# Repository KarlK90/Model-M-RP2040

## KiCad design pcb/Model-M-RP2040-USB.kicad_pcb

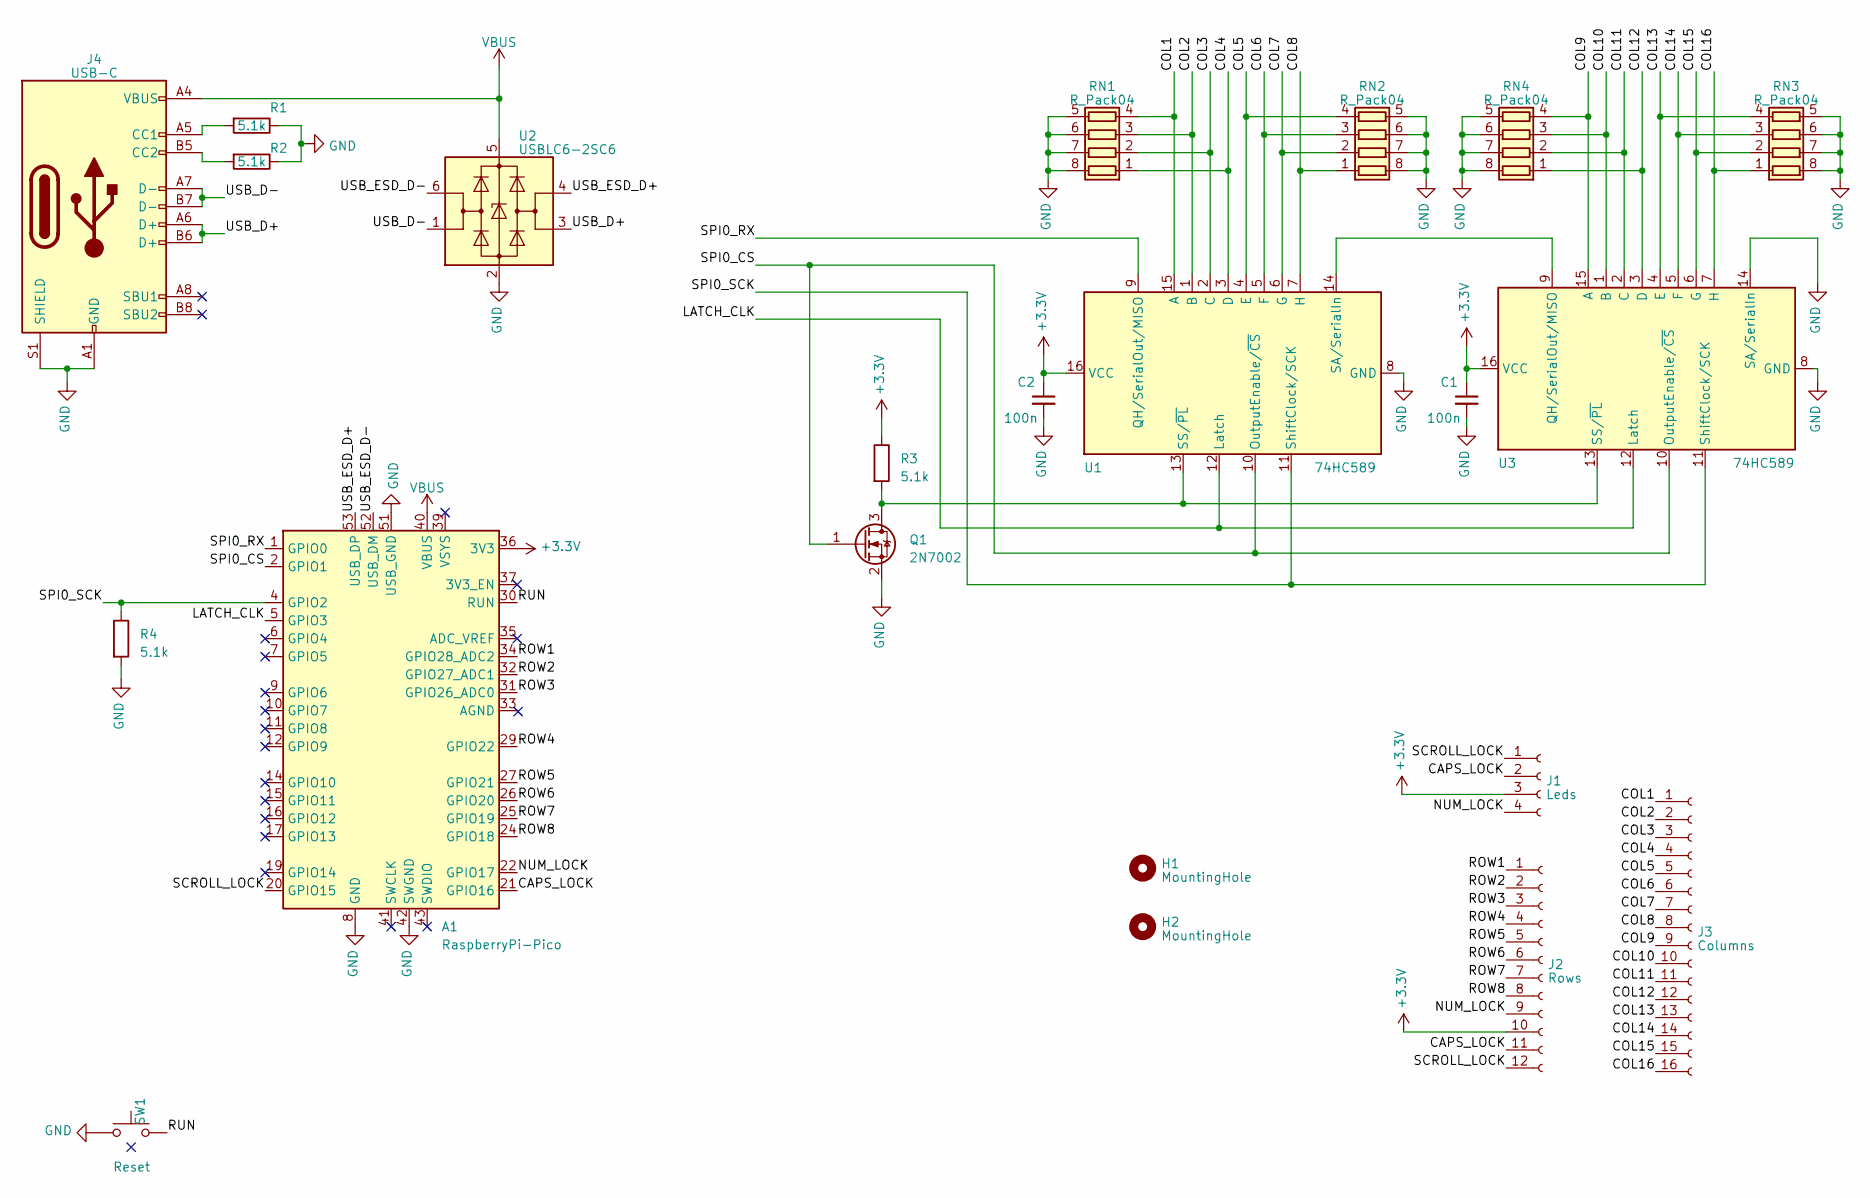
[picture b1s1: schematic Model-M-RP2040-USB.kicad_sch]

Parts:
A1: RaspberryPi-Pico; Raspberry_Pi_Pico_SMT_THT
C1, C2: 100n; C_0603_1608Metric
H1, H2: MountingHole; MountingHole_3.5mm
J1: Leds; PinSocket_1x04_P2.54mm_Vertical
J2: Rows; PinSocket_1x12_P2.54mm_Vertical
J3: Columns; PinSocket_1x16_P2.54mm_Vertical
J4: USB-C; HRO-TYPE-C-31-M-12-HandSoldering-NoSBU
Q1: 2N7002; SOT-23
R1, R2, R3, R4: 5.1k; R_0603_1608Metric
RN1, RN2, RN3, RN4: R_Pack04; R_Array_Convex_4x0603
SW1: Reset; TC-1109DE-X-X
U1, U3: 74HC589; SOIC-16_3.9x9.9mm_P1.27mm
U2: USBLC6-2SC6; SOT-23-6

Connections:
+3V3: A1.36 (3V3), C1.1, C2.1, J1.3, J2.10, R3.1, U1.16 (VCC), U3.16 (VCC)
/CAPS_LOCK: A1.21 (GPIO16), J1.2, J2.11
/COL1: J3.1, RN1.4 (R4.1), U1.15 (A)
/COL2: J3.2, RN1.3 (R3.1), U1.1 (B)
/COL3: J3.3, RN1.2 (R2.1), U1.2 (C)
/COL4: J3.4, RN1.1 (R1.1), U1.3 (D)
/COL5: J3.5, RN2.4 (R4.1), U1.4 (E)
/COL6: J3.6, RN2.3 (R3.1), U1.5 (F)
/COL7: J3.7, RN2.2 (R2.1), U1.6 (G)
/COL8: J3.8, RN2.1 (R1.1), U1.7 (H)
/COL9: J3.9, RN4.4 (R4.1), U3.15 (A)
/COL10: J3.10, RN4.3 (R3.1), U3.1 (B)
/COL11: J3.11, RN4.2 (R2.1), U3.2 (C)
/COL12: J3.12, RN4.1 (R1.1), U3.3 (D)
/COL13: J3.13, RN3.4 (R4.1), U3.4 (E)
/COL14: J3.14, RN3.3 (R3.1), U3.5 (F)
/COL15: J3.15, RN3.2 (R2.1), U3.6 (G)
/COL16: J3.16, RN3.1 (R1.1), U3.7 (H)
/LATCH_CLK: A1.5 (GPIO3), U1.12 (Latch), U3.12 (Latch)
/NUM_LOCK: A1.22 (GPIO17), J1.4, J2.9
/ROW1: A1.34 (GPIO28_ADC2), J2.1
/ROW2: A1.32 (GPIO27_ADC1), J2.2
/ROW3: A1.31 (GPIO26_ADC0), J2.3
/ROW4: A1.29 (GPIO22), J2.4
/ROW5: A1.27 (GPIO21), J2.5
/ROW6: A1.26 (GPIO20), J2.6
/ROW7: A1.25 (GPIO19), J2.7
/ROW8: A1.24 (GPIO18), J2.8
/RUN: A1.30 (RUN), SW1.2
/SCROLL_LOCK: A1.20 (GPIO15), J1.1, J2.12
/SPI0_CS: A1.2 (GPIO1), Q1.1 (G), U1.10 (OutputEnable/~CS), U3.10 (OutputEnable/~CS)
/SPI0_RX: A1.1 (GPIO0), U1.9 (QH/SerialOut/MISO)
/SPI0_SCK: A1.4 (GPIO2), R4.1, U1.11 (ShiftClock/SCK), U3.11 (ShiftClock/SCK)
/USB_D+: J4.A6 (D+), J4.B6 (D+), U2.3 (I/O2)
/USB_D-: J4.A7 (D-), J4.B7 (D-), U2.1 (I/O1)
/USB_ESD_D+: A1.53 (USB_DP), U2.4 (I/O2)
/USB_ESD_D-: A1.52 (USB_DM), U2.6 (I/O1)
GND: A1.3 (GND), A1.8 (GND), A1.13 (GND), A1.18 (GND), A1.23 (GND), A1.28 (GND), A1.38 (GND), A1.42 (SWGND), A1.51 (USB_GND), C1.2, C2.2, J4.A1 (GND), J4.A12 (GND), J4.B1 (GND), J4.B12 (GND), J4.S1 (SHIELD), Q1.2 (S), R1.1, R2.1, R4.2, RN1.5 (R4.2), RN1.6 (R3.2), RN1.7 (R2.2), RN1.8 (R1.2), RN2.5 (R4.2), RN2.6 (R3.2), RN2.7 (R2.2), RN2.8 (R1.2), RN3.5 (R4.2), RN3.6 (R3.2), RN3.7 (R2.2), RN3.8 (R1.2), RN4.5 (R4.2), RN4.6 (R3.2), RN4.7 (R2.2), RN4.8 (R1.2), SW1.1, U1.8 (GND), U2.2 (GND), U3.8 (GND), U3.14 (SA/SerialIn)
unnamed: J4.A5 (CC1), R1.2
unnamed: J4.B5 (CC2), R2.2
unnamed: Q1.3 (D), R3.2, U1.13 (SS/~PL), U3.13 (SS/~PL)
unnamed: U1.14 (SA/SerialIn), U3.9 (QH/SerialOut/MISO)
VBUS: A1.40 (VBUS), J4.A4 (VBUS), J4.A9 (VBUS), J4.B4 (VBUS), J4.B9 (VBUS), U2.5 (VBUS)

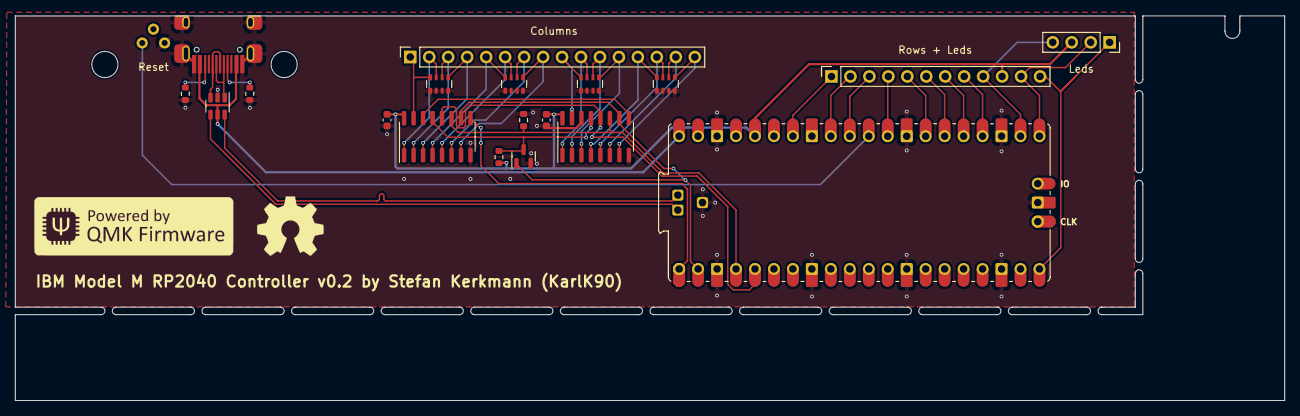
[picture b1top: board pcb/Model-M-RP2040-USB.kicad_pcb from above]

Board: 2 copper layers, 170.0 x 51.5 mm, 22 parts (0 on the bottom side), 43 nets.

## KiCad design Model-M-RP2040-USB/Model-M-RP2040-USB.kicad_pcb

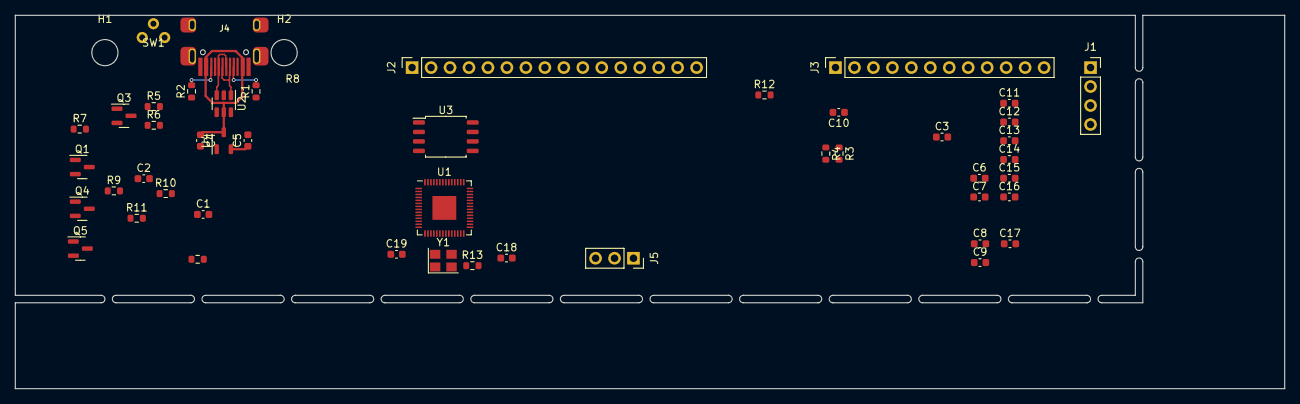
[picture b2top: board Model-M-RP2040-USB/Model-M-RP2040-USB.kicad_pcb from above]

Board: 2 copper layers, 170.0 x 50.0 mm, 49 parts (1 on the bottom side), 51 nets.

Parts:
C1: 4u7; C_0603_1608Metric
C2, C4, C5: 10u; C_0603_1608Metric
C3, C6, C7, C8, C9, C10, C11, C12, C13, C15, C16: 100n; C_0603_1608Metric
C14, C17: 1u; C_0603_1608Metric
C18, C19: 22p; C_0603_1608Metric
H1, H2: MountingHole; MountingHole_3.5mm
J1: Leds; PinSocket_1x04_P2.54mm_Vertical
J2: Rows; PinSocket_1x16_P2.54mm_Vertical
J3: Columns; PinSocket_1x12_P2.54mm_Vertical
J4: USB-C; HRO-TYPE-C-31-M-12-HandSoldering-NoSBU
J5: SWD; PinSocket_1x03_P2.54mm_Vertical
Q1, Q3, Q4, Q5: 2N7002; SOT-23
R1, R2: 5.1k; R_0603_1608Metric
R3, R4: 27; R_0603_1608Metric
R5, R6, R7, R12: 10k; R_0603_1608Metric
R8: 51K; R_0603_1608Metric
R9, R10: 51k; R_0603_1608Metric
R11, R13: 1k; R_0603_1608Metric
SW1: SWITCH; TC-1109DE-X-X
U1: RP2040; QFN-56-1EP_7x7mm_P0.4mm_EP3.2x3.2mm
U2: USBLC6-2SC6; SOT-23-6
U3: W25Q128JVS; SOIC-8_5.23x5.23mm_P1.27mm
U4: XC6206P332MR; SOT-23-3
Y1: 12MHz; Crystal_SMD_3225-4Pin_3.2x2.5mm

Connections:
+1V1: C15.1, C16.1, C17.1, U1.23 (DVDD), U1.45 (VREG_VOUT), U1.50 (DVDD)
+3V3: C3.1, C5.1, C6.1, C7.1, C8.1, C9.1, C10.1, C11.1, C12.1, C13.1, C14.1, J1.3, R5.1, R6.1, R7.1, R12.1, U1.1 (IOVDD), U1.10 (IOVDD), U1.22 (IOVDD), U1.33 (IOVDD), U1.42 (IOVDD), U1.43 (ADC_AVDD), U1.44 (VREG_IN), U1.48 (USB_VDD), U1.49 (IOVDD), U3.8 (VCC), U4.2 (VO)
/BOOT: Q5.3 (D), R11.2
/CAPS_LOCK: J1.2, U1.37 (GPIO25)
/COL1: J3.1, U1.11 (GPIO8)
/COL2: J3.2, U1.12 (GPIO9)
/COL3: J3.3, U1.13 (GPIO10)
/COL4: J3.4, U1.14 (GPIO11)
/COL5: J3.5, U1.15 (GPIO12)
/COL6: J3.6, U1.16 (GPIO13)
/COL7: J3.7, U1.17 (GPIO14)
/COL8: J3.8, U1.18 (GPIO15)
/COL9: J3.9, U1.27 (GPIO16)
/COL10: J3.10, U1.28 (GPIO17)
/COL11: J3.11, U1.29 (GPIO18)
/COL12: J3.12, U1.30 (GPIO19)
/NUM_LOCK: J1.4, U1.38 (GPIO26_ADC0)
/QSPI_SCLK: U1.52 (QSPI_SCLK), U3.6 (CLK)
/QSPI_SD0: U1.53 (QSPI_SD0), U3.5 (DI(IO0))
/QSPI_SD1: U1.55 (QSPI_SD1), U3.2 (DO(IO1))
/QSPI_SD2: U1.54 (QSPI_SD2), U3.3 (IO2)
/QSPI_SD3: U1.51 (QSPI_SD3), U3.7 (IO3)
/QSPI_SS: R11.1, R12.2, U1.56 (QSPI_SS), U3.1 (~CS)
/RESET: Q3.1 (G), R5.2, SW1.2
/ROW1: J2.1, U1.2 (GPIO0)
/ROW2: J2.2, U1.3 (GPIO1)
/ROW3: J2.3, U1.4 (GPIO2)
/ROW4: J2.4, U1.5 (GPIO3)
/ROW5: J2.5, U1.6 (GPIO4)
/ROW6: J2.6, U1.7 (GPIO5)
/ROW7: J2.7, U1.8 (GPIO6)
/ROW8: J2.8, U1.9 (GPIO7)
/RUN: Q1.3 (D), R7.2, U1.26 (RUN)
/SCROLL_LOCK: J1.1, U1.36 (GPIO24)
/SWCLK: J5.2, U1.24 (SWCLK)
/SWDIO: J5.1, U1.25 (SWD)
/USB_D+: J4.A6 (D+), J4.B6 (D+), R3.1, U2.3 (I/O2), U2.4 (I/O2)
/USB_D-: J4.A7 (D-), J4.B7 (D-), R4.1, U2.1 (I/O1), U2.6 (I/O1)
GND: C1.2, C2.2, C3.2, C4.2, C5.2, C6.2, C7.2, C8.2, C9.2, C10.2, C11.2, C12.2, C13.2, C14.2, C15.2, C16.2, C17.2, C18.1, C19.1, J4.A1 (GND), J4.B1 (GND), J4.S1 (SHIELD), J5.3, Q1.2 (S), Q3.2 (S), Q5.2 (S), R1.1, R2.1, R10.2, SW1.1, U1.19 (TESTEN), U1.57 (GND), U2.2 (GND), U3.4 (GND), U4.1 (GND), Y1.2, Y1.4
unnamed: C19.2, R13.1, Y1.3
unnamed: J4.A5 (CC1), R1.2
unnamed: J4.B5 (CC2), R2.2
unnamed: Q1.1 (G), Q3.3 (D), Q4.1 (G), Q4.2 (S), R6.2
unnamed: Q4.3 (D), R8.1
unnamed: C1.1, C2.1, Q5.1 (G), R8.2, R9.1
unnamed: R9.2, R10.1
unnamed: R4.2, U1.46 (USB_DM)
unnamed: R3.2, U1.47 (USB_DP)
unnamed: C18.2, U1.20 (XIN), Y1.1
unnamed: R13.2, U1.21 (XOUT)
VBUS: C4.1, J4.A4 (VBUS), J4.B4 (VBUS), U2.5 (VBUS), U4.3 (VI)

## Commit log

2023-04-03 Add incomplete version with on-board MCU
    This commit is the last checkpoint before switching to a version which
    simply uses a RPI pico dev board.
2023-04-03 WIP2
2023-04-19 Rev 0.2
